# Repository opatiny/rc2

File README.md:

# Remote Control Cylinder

---
Link to "site": https://opatiny.github.io/rc2/.

__WARNING:__ This README is not the main source of information for this project. A detailled paper can be found [here](https://github.com/opatiny/rc2/blob/master/documentation/RemoteControlCylinder.pdf).

_Final cylinder prototype_

## Cite this repository

Océane Patiny, & Luc Patiny. (2020, October 3). opatiny/rc2: Remote controlled cylinder final documentation (Version v1.0.0). Zenodo. http://doi.org/10.5281/zenodo.4064763

## Abstract
This one year project consists in the development of a remote controlled cylinder that uses servo motors to displace its center of mass, which leads the cylinder to accelerate linearly. This implies that very diversified fields such as mathematics, physics, programming, electronics and mechanics had to be explored and partly understood to be combined in the final prototype. This prototype has an acrylic glass base structure with a diameter of 32 cm, it is controlled using a C.H.I.P. Pro (a micro-controller similar to Raspberry Pi) and a customized dedicated extension board. The board includes a driver for four servo motors and a 6 axis accelerometer. Finally, the power supply consists of a pack of three AA batteries. All the programming was made using JavaScript scripts that are run using Node.js and a Shell. In addition, the cylinder is remotely controlled through a web page, which make it easy and intuitive for the user. The final features of this robotic cylinder are the following: it can roll forwards and backwards, stop and keep itself balanced on a gentle slope . Also, it is only working well on flat, hard surfaces, though it could easily be adapted to rougher surfaces. The possibility has also been considered of creating a sphere that uses the same technologies as the cylinder that was constructed in this project. The results of the project can be seen easily in [this movie](https://youtu.be/QggOjoGjJhA).

## Liscence

Finally, this work is meant to be as open-source as possible. Therefore, the software that was developed is under MIT licence, whereas the hardware is under CERN OHL.

## Concept

Initially the project was inspired by a rover realized by [Octanis](https://www.octanis.org/), a student's association specialized in electronics. The rover was supposed to be send to Antarctica and be able to analyse it's environment autonomously. Seeing the Rover tested on a Glacier on a windy day made me wonder what would be the best design for a windproof robot and I immediately thought of a spherical robot. However, once I got back home and looked for similar ideas, I realized that they were already existing projects that consisted in a spherical robot. One of the most famous being the [Sphero](https://www.sphero.com/), a spherical robot toy.

Looking further, I also realized that most of the projects use a similar approach to move the sphere: I call it the hamster wheel approach. It basically is a little car which wheels lay on the outer, rigid shell that induces the movement. I, on the contrary, had imagined a completely different system: I would displace the center of mass of the cylinder to make it roll.

## Programming

All the code that allows the control of the cylinder is contained in the following repository:
[https://github.com/opatiny/rpi-cylinder](https://github.com/opatiny/rpi-cylinder).

The programming has been done in JavaScript (using Node.js) and HTML for the web page that allows the control of the cylinder. Websocket was used to make the web page dynamic.

## Documentation

You can find a lot mor documentation about this project in the [documentation](https://github.com/opatiny/rc2/tree/master/documentation) section of this repository. There, you will find pictures, a developed abstract, and the paper about this project.

## Videos

Cardboard model of the cylinder's mechanism: [https://youtu.be/4SuPhpwOK5g](https://youtu.be/4SuPhpwOK5g)

The mass of cylinderPrototype2 moving on a circle using an atMega32u4: [https://youtu.be/1zOCNZ_r5pY](https://youtu.be/1zOCNZ_r5pY)

Final cylinder's prototype presentation video:
[https://youtu.be/QggOjoGjJhA](https://youtu.be/QggOjoGjJhA)

## Repository structure

In this section, we explain what the different folders of this repository contain and what it was used for.

__Note:__ Three main prototypes were built during this project. To refer to them, we use the acronyms cp1, cp2 and cp3 ("cp" stands for "cylinderPrototype"). You can see pictures of the prototypes in the [Pictures section](#pictures).

### arduino
Very basic programs in Arduino that allowed to test the movement of the mass with cp2. The values of the angles of the servos motors depending on the mass position were exported from the [GeoGebra model](https://github.com/opatiny/rc2/blob/master/movingMassOnCircle/geogebra/cylinderPrototype2/cylinderPrototype2.ggb) that we designed.

### datasheets
Datasheets of the electronical components used in this project: servo motors (MG995), accelerometer (MPU6050), servos driver (PCA9685) and C.H.I.P..

### documentation
Main source of information about this project, contains a pdf of the paper, a presentation, posters and an abstract. You will also find pictures there.

### freecad
FreeCAD is the software we used to create the designs of the cylinder. The "exports" subfolder contains files that can be directly used to laser cut the different parts (.dxf).

### javascript
First JavaScript programs that implemented the mathematical formula that returns the angles of the servos depending on the position of the mass. This code is the base of the [chip](https://github.com/opatiny/chip) GitHub repository, which contains the final code.

### movingMassOnCircle
Contains the GeoGebra models of the cylinder's mass movement and files commenting the observations made based upon them.

### pcb
Contains the Eagle and KiCAD files of the extension boards. They are two different boards, because when working on the project after a year, I realized that the cylinder was no longer functionning. I therefore had to change the micro-controller, because C.H.I.P. had made bankrupt. I decided to switch to a Raspberry Pi Nano W.

### raspberry
Procedure allowing to format a Raspberry Pi to make it act as a WiFi rooter.

## Pictures

Here are a few pictures of the project.

_Cardboard model of the cylinder_

_First prototype of the cylinder_

_[GeoGebra](https://www.geogebra.org/) model allowing to see the movement of the servo motors_

_Close-up of the second prototype_

_Metal turning a part of cp3_

_PCB extension allowing the connection of two I2C peripherals to the C.H.I.P. Pro (accelerometer and servo driver)_

_Long aperture picture of the mass moving on a spiral (cp3), max radius is 40mm_

_Final control web page_

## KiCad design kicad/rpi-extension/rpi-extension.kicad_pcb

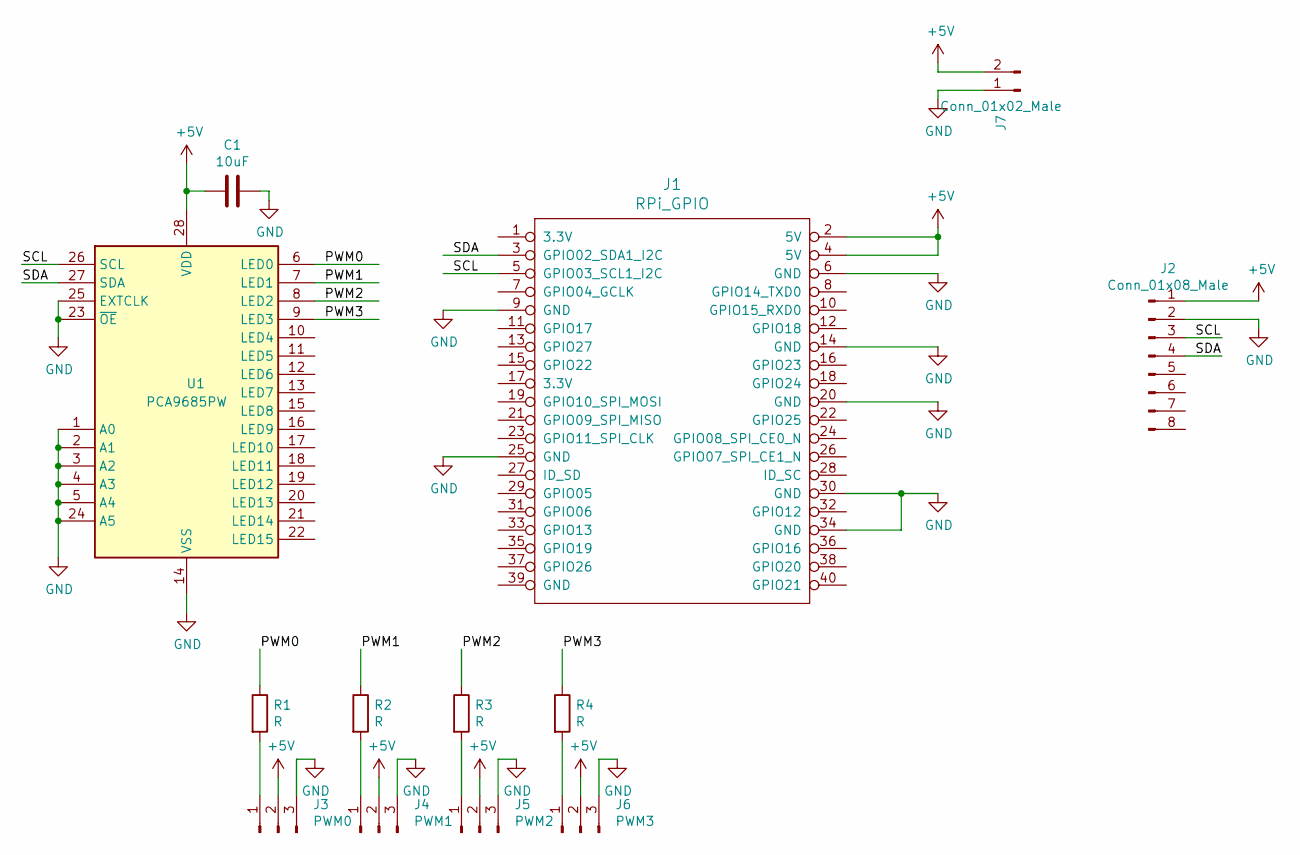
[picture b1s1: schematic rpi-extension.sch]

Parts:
C1: 10uF; C_0805_2012Metric_Pad1.15x1.40mm_HandSolder
J1: RPi_GPIO; PinSocket_2x20_P2.54mm_Vertical
J2: Conn_01x08_Male; PinHeader_1x08_P2.54mm_Vertical
J3: PWM0; PinHeader_1x03_P2.54mm_Vertical
J4: PWM1; PinHeader_1x03_P2.54mm_Vertical
J5: PWM2; PinHeader_1x03_P2.54mm_Vertical
J6: PWM3; PinHeader_1x03_P2.54mm_Vertical
J7: Conn_01x02_Male; Molex_KK-254_AE-6410-02A_1x02_P2.54mm_Vertical
R1, R2, R3, R4: R; R_0805_2012Metric_Pad1.15x1.40mm_HandSolder
U1: PCA9685PW; TSSOP-28_4.4x9.7mm_P0.65mm

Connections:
+5V: C1.2, J1.2 (5V), J1.4 (5V), J2.1, J3.2, J4.2, J5.2, J6.2, J7.2, U1.28 (VDD)
/PWM0: R1.1, U1.6 (LED0)
/PWM1: R2.1, U1.7 (LED1)
/PWM2: R3.1, U1.8 (LED2)
/PWM3: R4.1, U1.9 (LED3)
/SCL: J1.5 (GPIO03_SCL1_I2C), J2.3, U1.26 (SCL)
/SDA: J1.3 (GPIO02_SDA1_I2C), J2.4, U1.27 (SDA)
GND: C1.1, J1.6 (GND), J1.9 (GND), J1.14 (GND), J1.20 (GND), J1.25 (GND), J1.30 (GND), J1.34 (GND), J2.2, J3.3, J4.3, J5.3, J6.3, J7.1, U1.1 (A0), U1.2 (A1), U1.3 (A2), U1.4 (A3), U1.5 (A4), U1.14 (VSS), U1.23 (~OE), U1.24 (A5), U1.25 (EXTCLK)
unnamed: J3.1, R1.2
unnamed: J4.1, R2.2
unnamed: J5.1, R3.2
unnamed: J6.1, R4.2

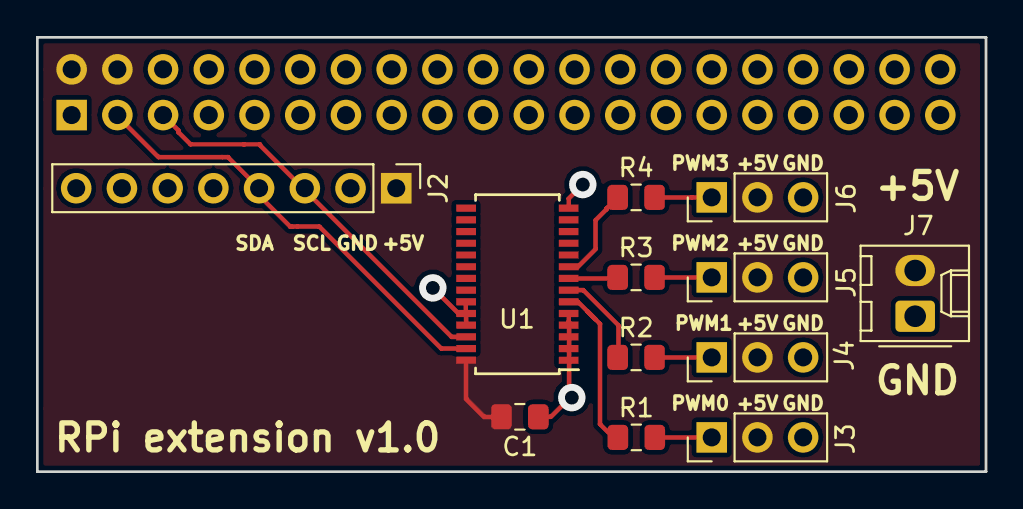
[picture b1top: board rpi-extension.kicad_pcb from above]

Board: 2 copper layers, 52.7 x 24.1 mm, 13 parts (1 on the bottom side), 12 nets.

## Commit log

2016-10-17 Datasheet MPU-6050 accelerometer - gyroscope
2016-10-17 Add initial freecad files
2016-10-17 Add servo oscilloscope
2016-10-19 Add high speed
2016-11-28 reorganising directories
2016-11-28 move files
2016-11-28 editing the readme
2016-11-28 readme changes
2016-12-19 Ordering directories
2016-12-19 add convert wolfram
2016-12-20 fix bug of ) ( not converted to ) * (
2016-12-30 working on code and adding .idea
2016-12-30 testing committing
2017-01-05 adding pictures
2017-01-16 modifing formula code
2017-01-18 modifing freecad document: wheel
2017-01-21 adding cylinder schemes in pictures
2017-01-29 modifing wheel and wheelAccessory (freecad)
2017-02-11 add gitignore file
2017-02-11 Remove unused files
2017-02-11 Add test code for understand code
2017-02-11 trying to understand formulas in code
2017-02-13 new formula taken from wolfram
    the thee other ones are when the general signs varies and when the sign in the cos varies
2017-02-22 adding links to the README
2017-02-24 Ordering pictures
2017-04-03 Adding new geogebra file. This is a first test of sovling the angles of the servo depending on the mass position, graphicaly.
2017-04-03 Adding datasheets
2017-04-05 Working on servosMovement
2017-04-05 Developing servos angles depending on position of the mass
2017-04-05 Adding "mess".
2017-04-08 First working moving servos
2017-04-10 Evolving servoMovement and adding pictures
2017-04-10 Adding presiceServoAxisTest text files
2017-04-10 Finally finding the limitation of the servo axis length!
2017-05-21 Adding physics and calculusScheme
2017-06-06 Modifing calculusScheme.key and adding squaredSquare
2017-06-18 Adding datasheets for alreadyExisting and working on circleAroundCenter with the geogebra approach.
2017-06-19 Adding pictures of prototype2 and upgrading calculusScheme.key.
2017-06-30 Organising movingMassOnCircle and adding schemes.
2017-06-30 Working on code
2017-07-03 Making the javascript code to have srevos angles depending on mass angle or position.
2017-07-03 Ordering files and adding pictures
2017-07-03 add ternary operator
2017-07-04 working on movingMassOnCircle
2017-07-04 work in progress
2017-07-06 Modifing cylinderDataKeynote.
2017-07-12 Working on eagle.
2017-07-13 Adding holes to the PCB on eagle and enhancing the freeca model of cylinder prototype 3.
2017-07-14 Adding jumper to eagle files and enhancing the freecad model of cylinderPrototype3.
2017-07-15 improve eagle design
2017-07-21 adapt the commandLineFunctions to cylinderPrototype3
2017-07-22 add pictures and modify keynotes.
2017-07-23 modify cylinderDataKeynote
2017-07-24 add rapporteur.pdf to pictures.
2017-08-16 add the pdf of speedFunctionScheme.
2017-08-18 adapt the javascript function returnAngleOnMassAngle.js to export values to spreadsheet
2017-08-18 add the keynote related to the pcb
2017-08-20 upgrade mess
2017-09-10 modify infos that come with the geogebra data
2017-09-22 add picture to parametersTest to test if d can be bigger than R
2017-09-24 add many screenshots of the keynote documents
2017-10-01 ordering pdfs of keynote, modifying approach.key
2017-10-08 clean freecad
2017-10-09 add all export files from freecad
2017-10-10 add pdfs of freecad files, add laserCutter keynote
2017-10-13 Create LICENSE
2017-10-16 mainly modify with keynote exports
2017-10-29 work on keynotes
2017-10-29 work on keynote files
2017-11-01 add communicationSystem.key and modify geogebra model of cp2
2017-11-01 add web page pictures
2017-11-19 order whole git and suppress not important pictures
2019-03-02 add kicad of rpi extension
2019-03-03 add kicad extension
2019-03-03 add readme for rpi
2019-03-03 update procedure to install node
2019-03-05 started posters for SAJ
2019-03-07 work on posters
2019-03-10 update kicad for extension
2019-03-10 remove gerber files
2019-03-11 add image smallLed.pdf and pdf of oral presentation
2019-03-13 rearrange repo and work on README
2019-03-13 test commit
2019-03-15 remove useless files
2019-03-25 add documentation/speedResults
2019-03-25 add final compressed pdf to documentation
2019-03-26 work on documentation, add abstract
2019-03-28 Set theme jekyll-theme-minimal
2019-03-28 Set theme jekyll-theme-slate
2019-04-01 add Rdata and Rhistory in gitignore
2019-04-01 update poster and remove useless files
2019-04-02 enhance README
2019-04-02 remove renamed files
2019-04-04 finish posters
2019-04-04 replace poster keynote by pdf
2019-04-04 rename poster pdf file
2019-04-12 rename posters pdf and add flyer
2019-04-17 enhance raspberry doc
2019-07-08 update paper pdf
2019-09-06 Add files via upload
    svg and dxf files of cp3
2020-10-03 update readme link
2020-10-03 add citation to readme
